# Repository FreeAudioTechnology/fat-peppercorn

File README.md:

# peppercorn
Small active microphone amplifier for voice recordings with power feed for MEMS mic capsules

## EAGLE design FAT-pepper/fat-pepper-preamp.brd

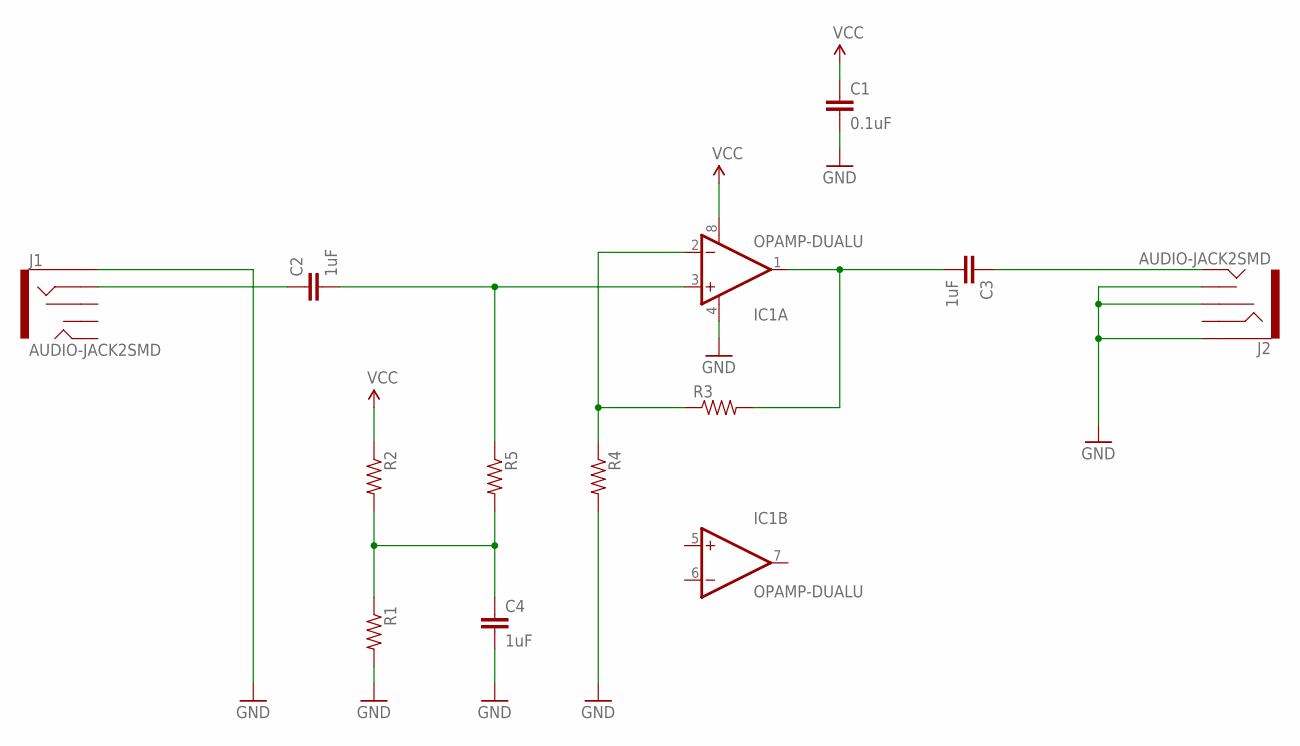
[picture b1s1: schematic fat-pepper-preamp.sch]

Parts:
C1: 0.1uF; 0402-CAP
C2, C3, C4: 1uF; 0603-CAP
IC1: OPAMP-DUALU; SO08
J1, J2: AUDIO-JACK2SMD; AUDIO-JACK-3.5MM-SMD
R1, R2, R3, R4, R5: RESISTOR0603-RES; 0603-RES

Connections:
GND: C1.2, C4.2, IC1.4 (V-), J1.SLEEVE, J2.RSH, J2.SLEEVE, J2.TSH, R1.2, R4.2
unnamed: C4.1, R1.1, R2.2, R5.2
unnamed: C2.2, IC1.3 (+IN), R5.1
unnamed: IC1.2 (-IN), R3.1, R4.1
unnamed: C3.2, IC1.1 (OUT), R3.2
unnamed: C3.1, J2.TIP
unnamed: C2.1, J1.RING
VCC: C1.1, IC1.8 (V+), R2.1

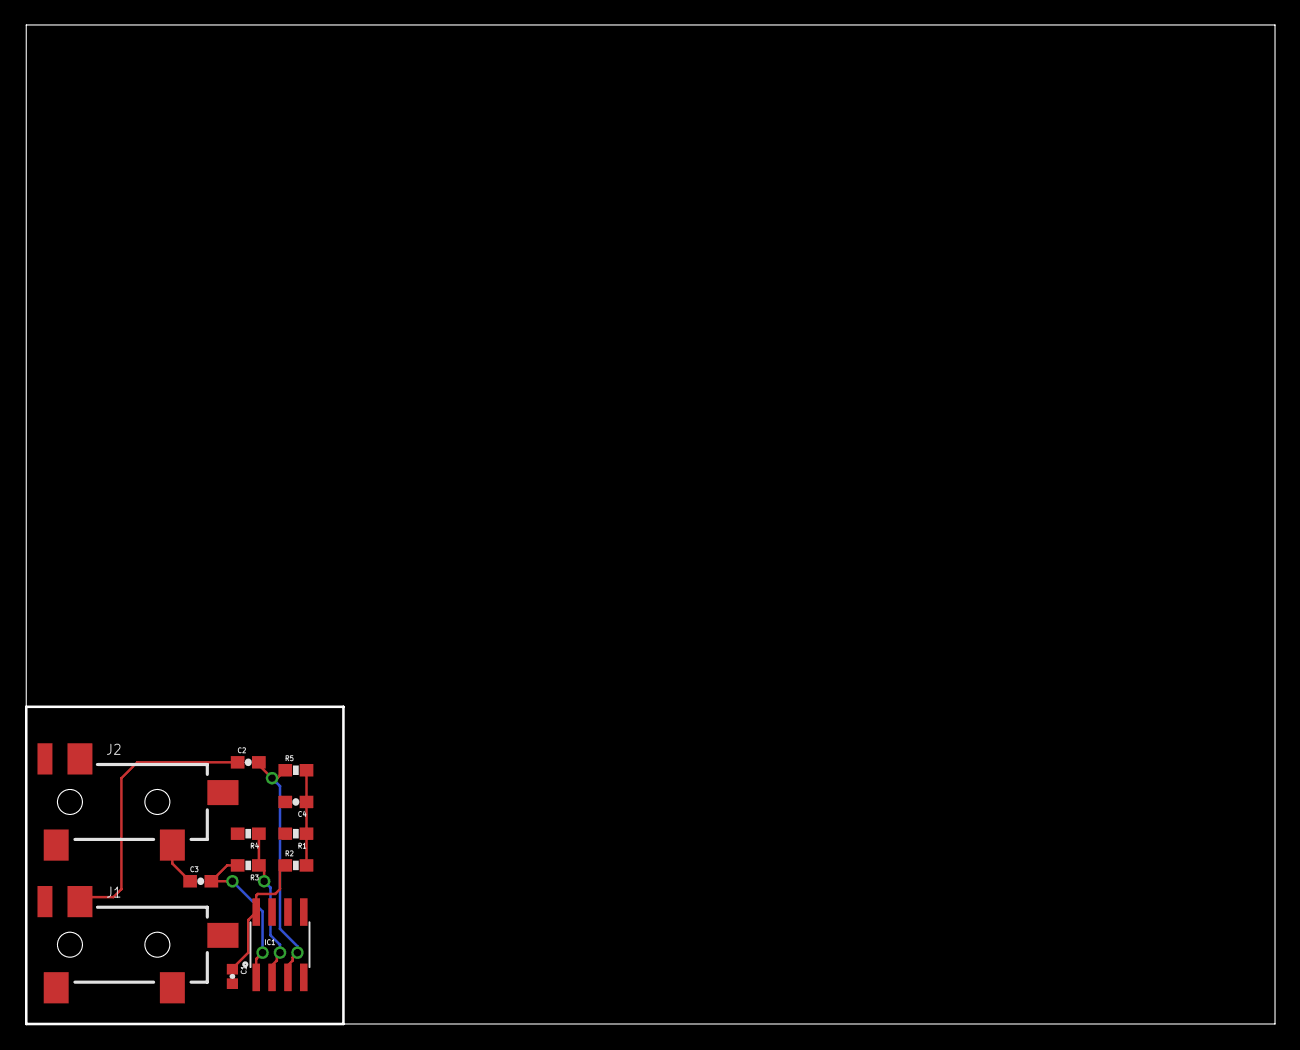
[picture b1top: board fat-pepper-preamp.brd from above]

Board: 2 copper layers, 100.0 x 80.0 mm, 12 parts (0 on the bottom side), 8 nets.

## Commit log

2016-05-30 Drafting a PCB layout [openwork https://youtu.be/K_E8CNicMC4]

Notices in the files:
parts and their libraries:
SparkFun-Capacitors: Licensing: Creative Commons ShareAlike 4.0 International - https://creativecommons.org/licenses/by-sa/4.0
